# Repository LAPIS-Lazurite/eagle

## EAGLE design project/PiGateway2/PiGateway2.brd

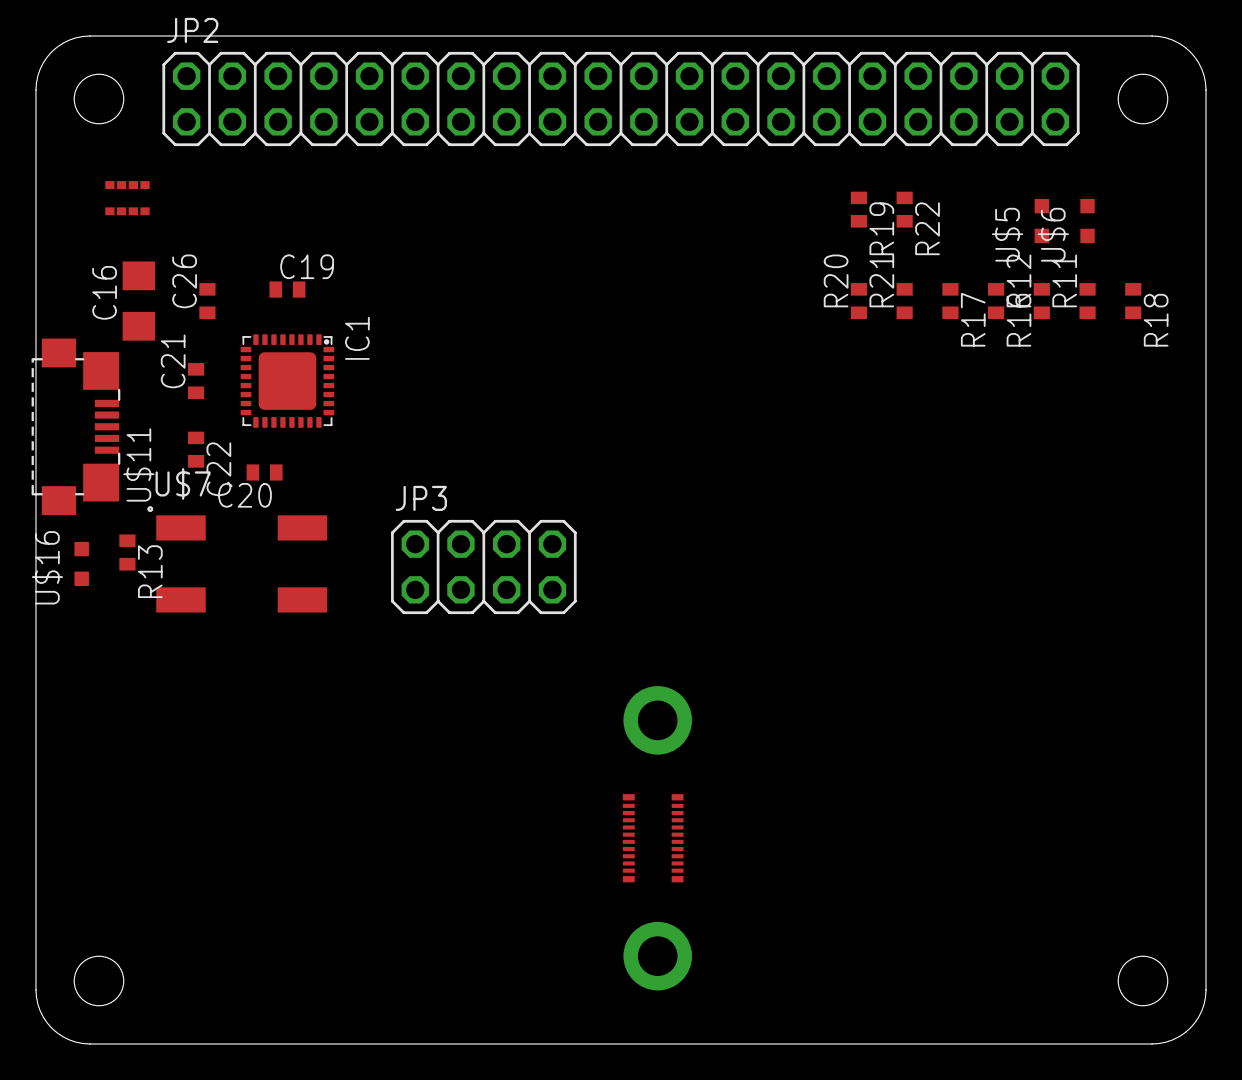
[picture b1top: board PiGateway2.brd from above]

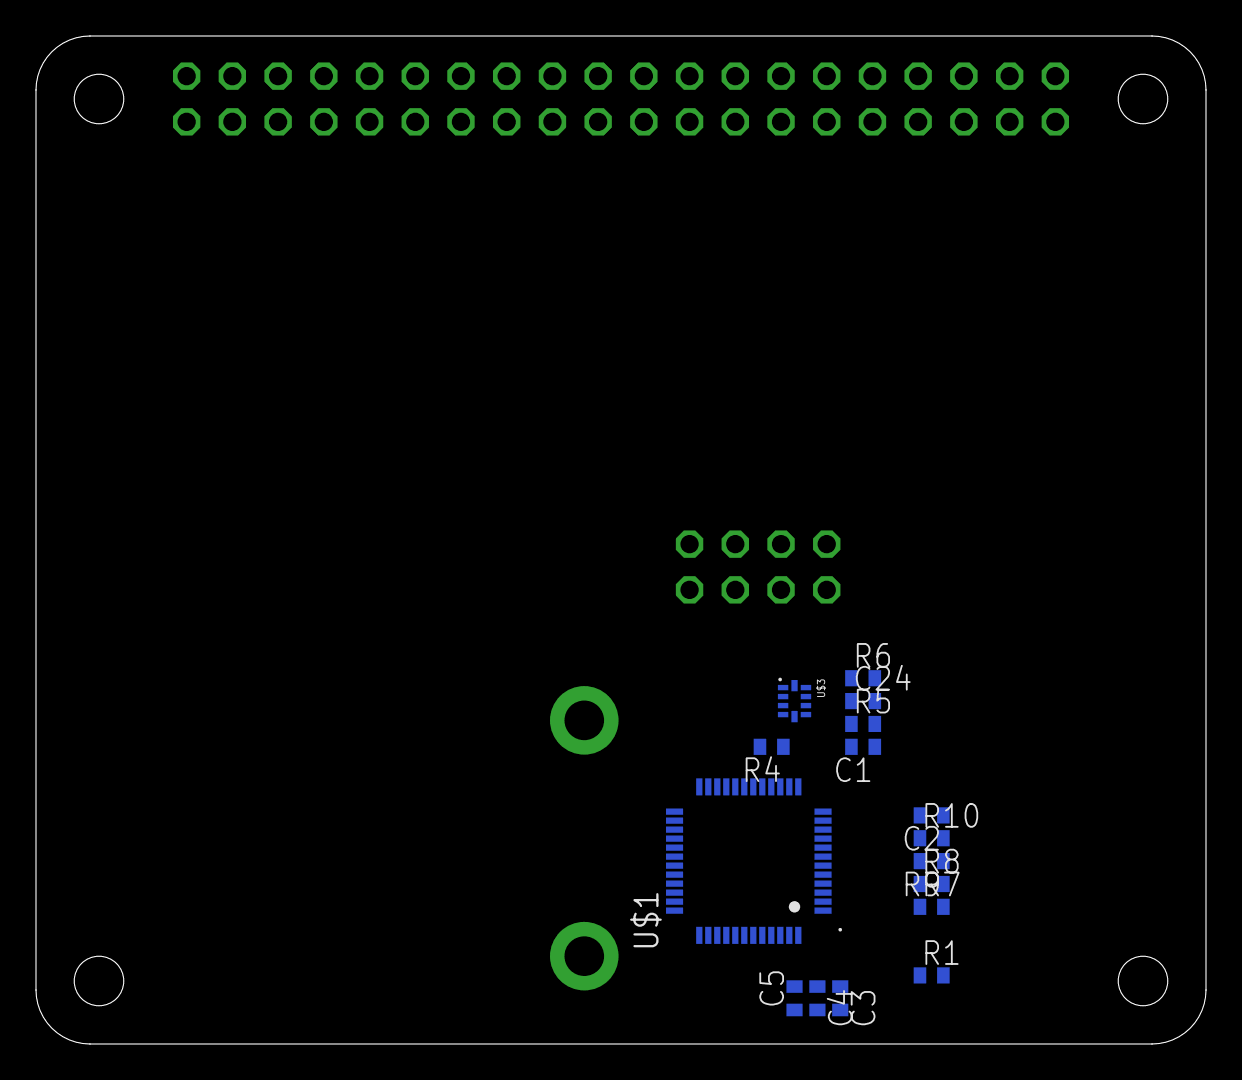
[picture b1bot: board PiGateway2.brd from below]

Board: 2 copper layers, 65.0 x 56.0 mm, 42 parts (16 on the bottom side), 46 nets, no tracks yet.

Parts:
C1, C19, C20, C24, C26: 0.1u; C0402
C2: 1u; C0402
C3: 33000p; C0402
C4, C5: 2.2u; C0402
C16: 22u; C1206
C21, C22: 47p; C0402
IC1: FT232RQ; QFN32
JP2: 2X20
JP3: 2X04
R1, R5, R6: 510; R0402
R4, R9, R10, R16, R17, R18, R19, R22: 10K; R0402
R7, R8, R11, R12, R13: 1K; R0402
R20: 0; R0402
R21: NC; R0402
U$1: ML620Q504
U$2: RT1A060AP; TSST8
U$3: TI-TS5A23159; UQFN10
U$4: DF40C-20DP-0.4V(51); BP3596A
U$5: SML-E13BC8T; SML-E1X
U$6: SML-E12Y8W; SML-E1X
U$7: SKHUALE010
U$11: ZX62R-B-5P
U$16: SML-E12U8WT86; SML-E1X

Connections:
+3V3: JP2.1, JP2.17, R11.1, R12.1, R16.1, R17.1, R18.1, R19.1, R22.1, U$4.8, U$4.9
+5V: JP2.2, JP2.4, U$2.P1, U$2.P2, U$2.P3, U$2.P6, U$2.P8
+5V/1: C1.1, C2.1, C5.1, C16.1, C19.1, C20.1, C24.1, C26.1, IC1.1, IC1.19, JP3.1, R9.1, R10.1, R13.2, U$1.12, U$1.13, U$1.44, U$2.P5, U$3.8, U$11.1
BOOT_WRITE: IC1.11, R4.1, U$3.1, U$3.5
DM: C22.1, IC1.15, U$11.2
DP: C21.1, IC1.14, U$11.3
GND: C1.2, C2.2, C3.2, C4.2, C5.2, C16.2, C19.2, C20.2, C21.2, C22.2, C24.2, C26.2, IC1.4, IC1.17, IC1.20, IC1.24, IC1.26, JP2.6, JP2.9, JP2.14, JP2.20, JP2.25, JP2.30, JP2.34, JP2.39, JP3.8, R4.2, U$1.14, U$1.45, U$3.3, U$4.3, U$4.4, U$4.5, U$4.6, U$4.17, U$4.GND1, U$7.3, U$7.4, U$11.4, U$11.5, U$11.M1, U$11.M2, U$11.M3, U$11.M4
I2C_SCL: JP2.5, R17.2, U$4.1
I2C_SDA: JP2.3, R16.2, U$4.2
LED_RX: JP2.33, U$6.C
LED_TX: JP2.31, U$5.C
MISO: JP2.21, U$4.12
MOSI: JP2.19, U$4.16
unnamed: C3.1, U$1.46
unnamed: IC1.32, U$3.2
unnamed: IC1.31, U$3.4
unnamed: IC1.30, R7.2
unnamed: C4.1, U$1.43
unnamed: R13.1, U$16.A
unnamed: IC1.2, R8.2
unnamed: IC1.22, R6.2
unnamed: IC1.21, R5.2
unnamed: R1.1, U$2.P4
unnamed: R11.2, U$6.A
unnamed: R12.2, U$5.A
P23: U$1.18, U$16.C
P30: R7.1, U$1.4
P31: R8.1, U$1.5
P34: JP3.5, R9.2, U$1.8
P35: JP3.6, R10.2, U$1.9
P36: JP3.4, U$1.10
P44: JP3.2, U$1.29
P45: JP3.3, U$1.30
P50: U$1.33, U$7.1, U$7.2
P53: JP3.7, U$1.36
RF_CSB: R20.1, R21.1, U$4.15
RF_CSB0: JP2.24, R19.2, R20.2
RF_CSB1: JP2.26, R21.2, R22.2
RF_IRQ: JP2.12, U$4.13
RF_REGPDIN: JP2.11, U$4.10
RF_RSTB: JP2.13, R18.2, U$4.11
SCLK: JP2.23, U$4.14
TEST0: U$1.41, U$3.10
TEST1N: U$1.42, U$3.6
U_TEST0: R6.1, U$3.9
U_TEST1N: R5.1, U$3.7

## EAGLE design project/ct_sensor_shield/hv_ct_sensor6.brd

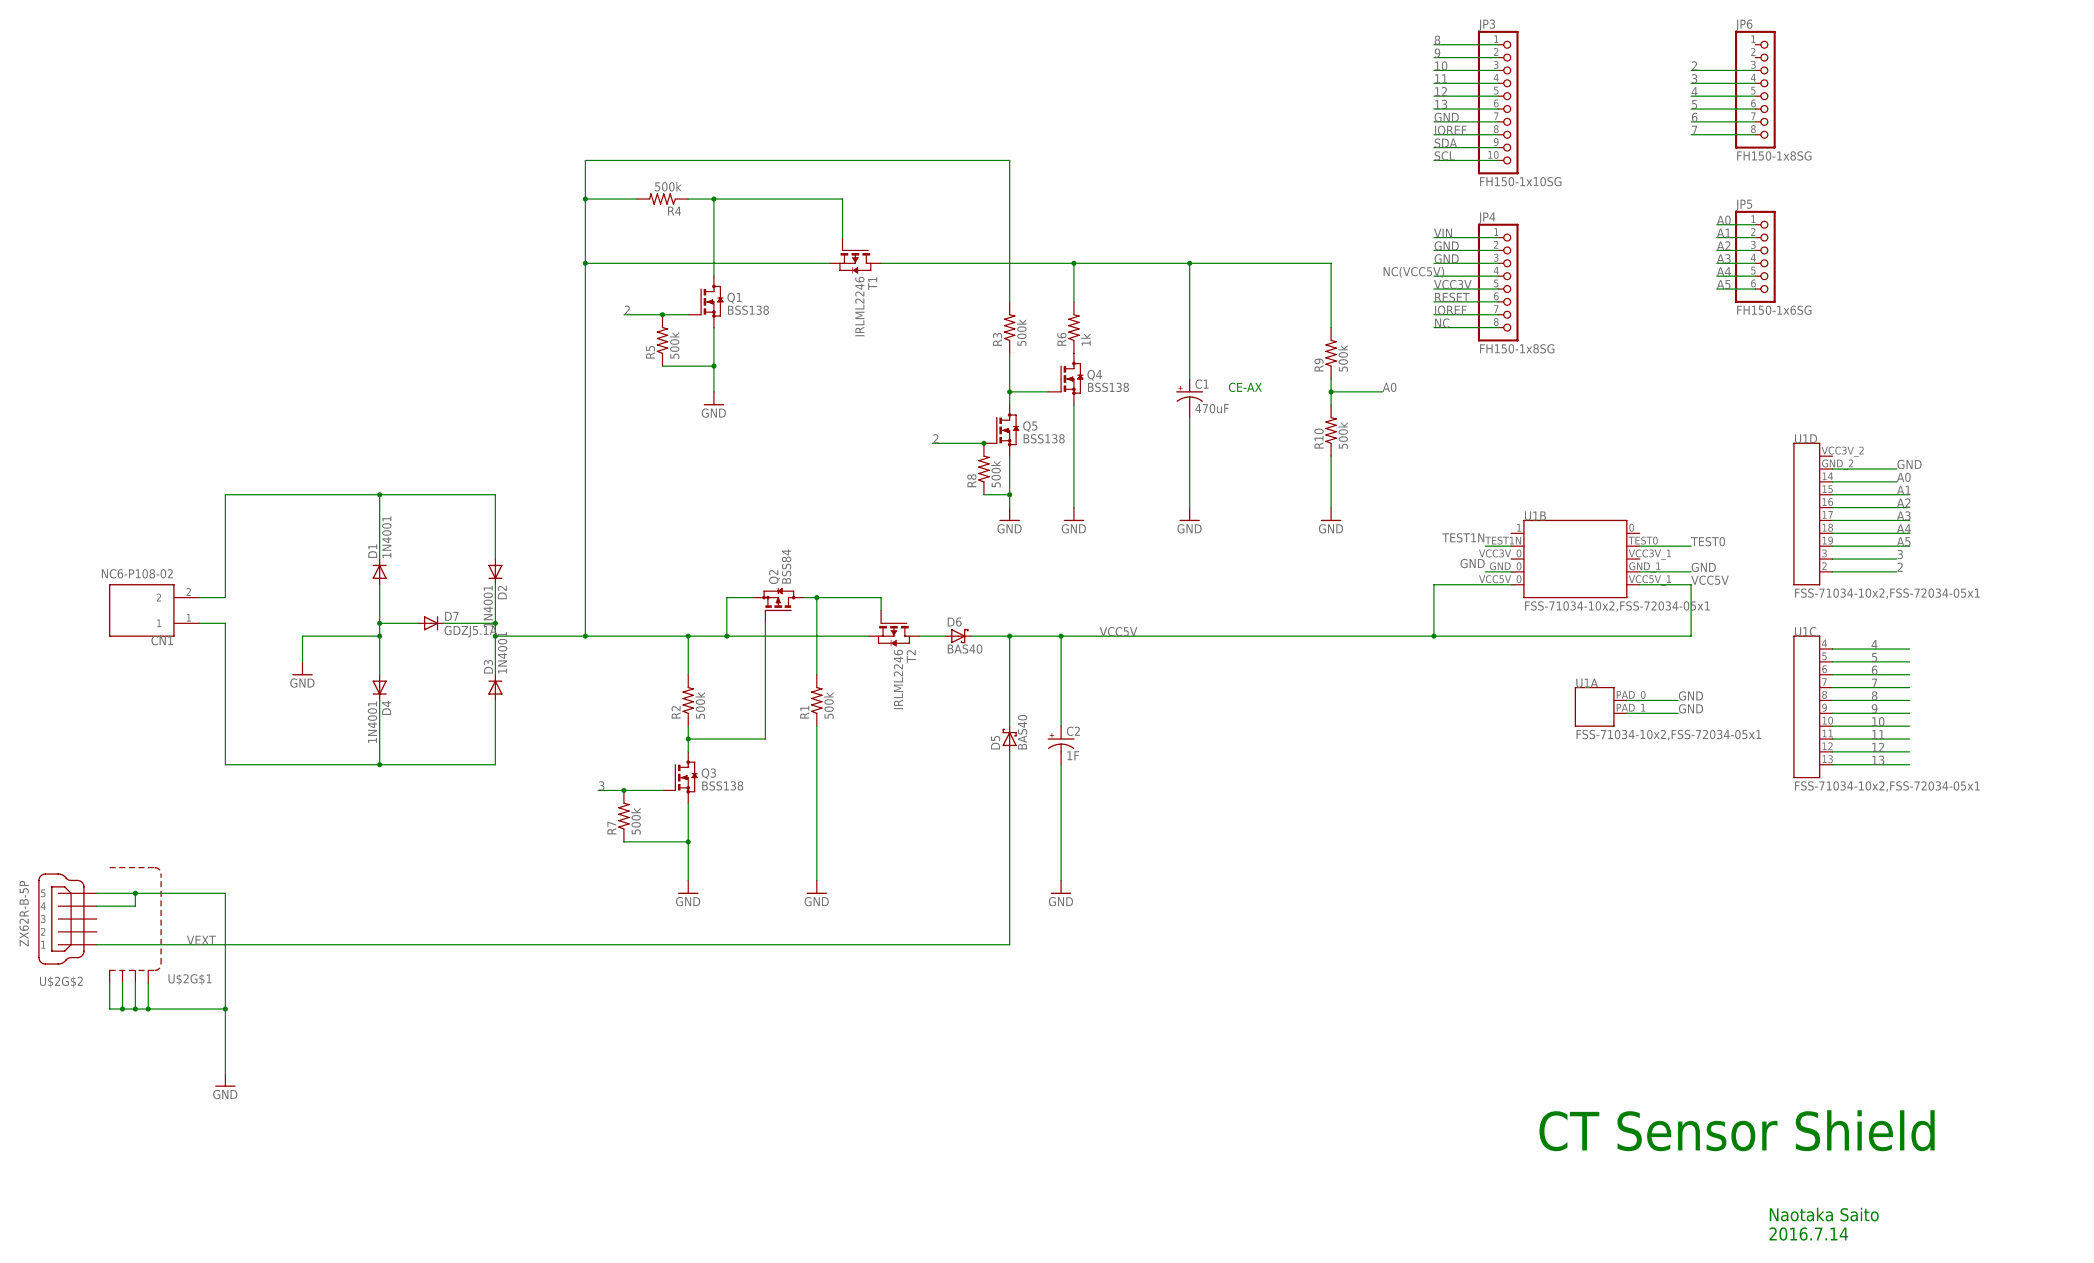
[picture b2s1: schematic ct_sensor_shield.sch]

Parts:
C1: 470uF; E5-10,5
C2: 1F; E5-20
CN1: NC6-P108-02; 2PIN
D1, D2, D3, D4: 1N4001; DO41-10
D5, D6: BAS40; SOT23
D7: GDZJ5.1A; DO34-7
JP3: FH150-1x10SG; 1X10
JP4, JP6: FH150-1x8SG; 1X08
JP5: FH150-1x6SG; 1X06
Q1, Q3, Q4, Q5: BSS138; SOT23
Q2: BSS84; SOT23
R1, R2, R3, R4, R5, R7, R8, R9, R10: 500k; R0603
R6: 1k; R0603
T1, T2: IRLML2246; SOT-23
U1: FSS-71034-10x2,FSS-72034-05x1; LAZURITE920J
U$2: ZX62R-B-5P

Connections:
2: JP6.3, Q1.1 (G), Q5.1 (G), R5.2, R8.2, U1.2
3: JP6.4, Q3.1 (G), R7.2, U1.3
4: JP6.5, U1.4
5: JP6.6, U1.5
6: JP6.7, U1.6
7: JP6.8, U1.7
8: JP3.1, U1.8
9: JP3.2, U1.9
10: JP3.3, U1.10
11: JP3.4, U1.11
12: JP3.5, U1.12
13: JP3.6, U1.13
A0: JP5.1, R9.1, R10.2, U1.14
A1: JP5.2, U1.15
A2: JP5.3, U1.16
A3: JP5.4, U1.17
A4: JP5.5, U1.18
A5: JP5.6, U1.19
GND: C1.-, C2.-, D1.A, D4.A, D7.A, JP3.7, JP4.2, JP4.3, Q1.2 (S), Q3.2 (S), Q4.2 (S), Q5.2 (S), R1.1, R5.1, R7.1, R8.1, R10.1, U1.GND_0, U1.GND_1, U1.GND_2, U1.PAD_0, U1.PAD_1, U$2.4, U$2.5, U$2.M1 (S1), U$2.M2 (S2), U$2.M3 (S3), U$2.M4 (S4)
I+: CN1.2, D1.C, D2.A
I-: CN1.1, D3.A, D4.C
IOREF: JP3.8, JP4.7
IOUT: D2.C, D3.C, D7.C, Q2.2 (S), R2.2, R3.2, R4.2, T1.2 (S), T2.2 (S)
IOUT2: D6.1 (A), T2.1 (D)
unnamed: Q2.3 (D), R1.2, T2.3 (G)
unnamed: Q2.1 (G), Q3.3 (D), R2.1
unnamed: Q1.3 (D), R4.1, T1.3 (G)
unnamed: Q4.3 (D), R6.1
unnamed: C1.+, R6.2, R9.2, T1.1 (D)
unnamed: Q4.1 (G), Q5.3 (D), R3.1
NC: JP4.8
NC(VCC5V): JP4.4
RESET: JP4.6
SCL: JP3.10
SDA: JP3.9
TEST0: U1.TEST0
TEST1N: U1.TEST1N
VCC3V: JP4.5
VCC5V: C2.+, D5.3 (C), D6.3 (C), U1.VCC5V_0, U1.VCC5V_1
VEXT: D5.1 (A), U$2.1
VIN: JP4.1

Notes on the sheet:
CE-AX
CT Sensor Shield
Naotaka Saito 2016.7.14

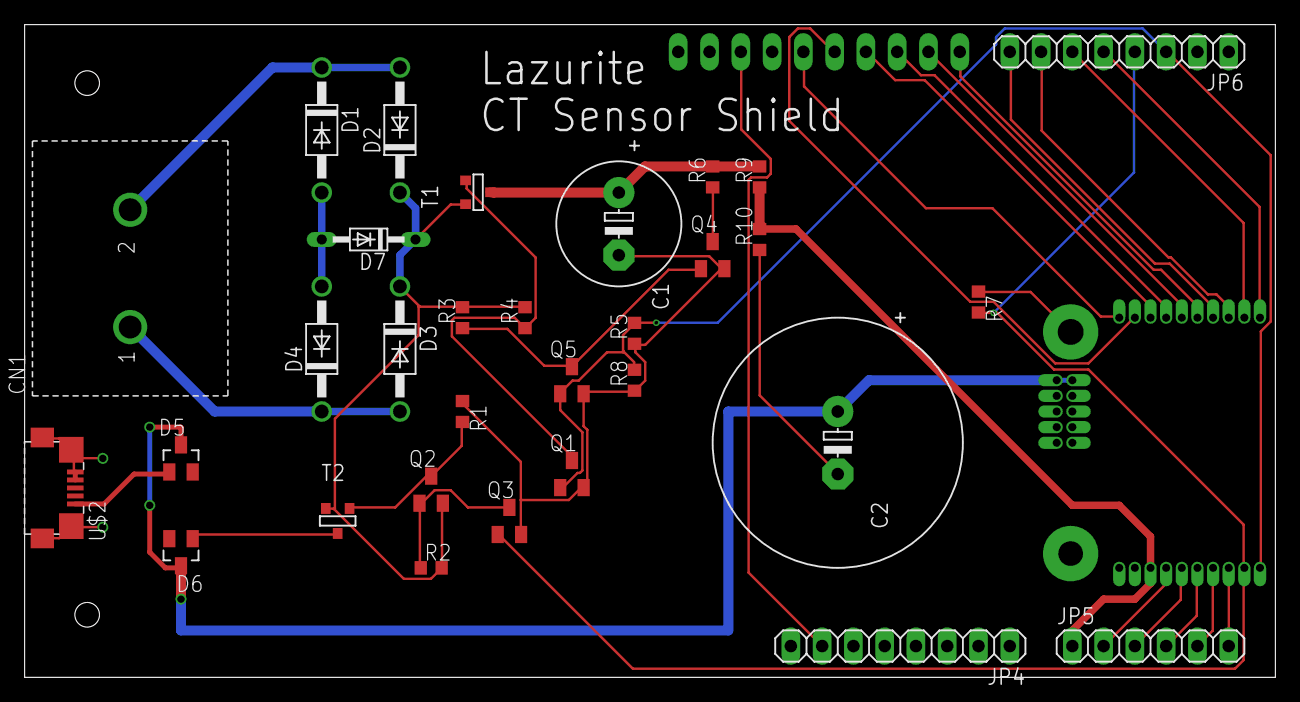
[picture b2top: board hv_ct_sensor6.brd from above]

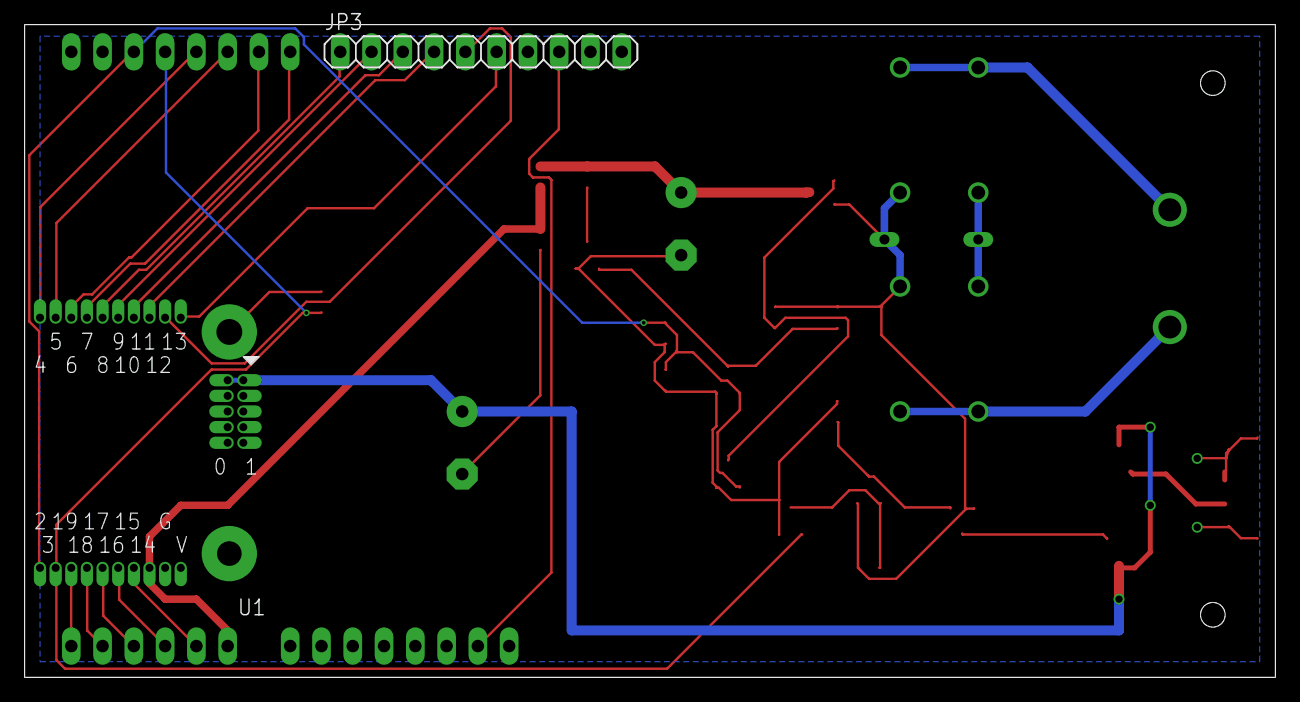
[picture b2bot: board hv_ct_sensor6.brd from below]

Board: 2 copper layers, 101.6 x 53.0 mm, 33 parts (2 on the bottom side), 32 nets.

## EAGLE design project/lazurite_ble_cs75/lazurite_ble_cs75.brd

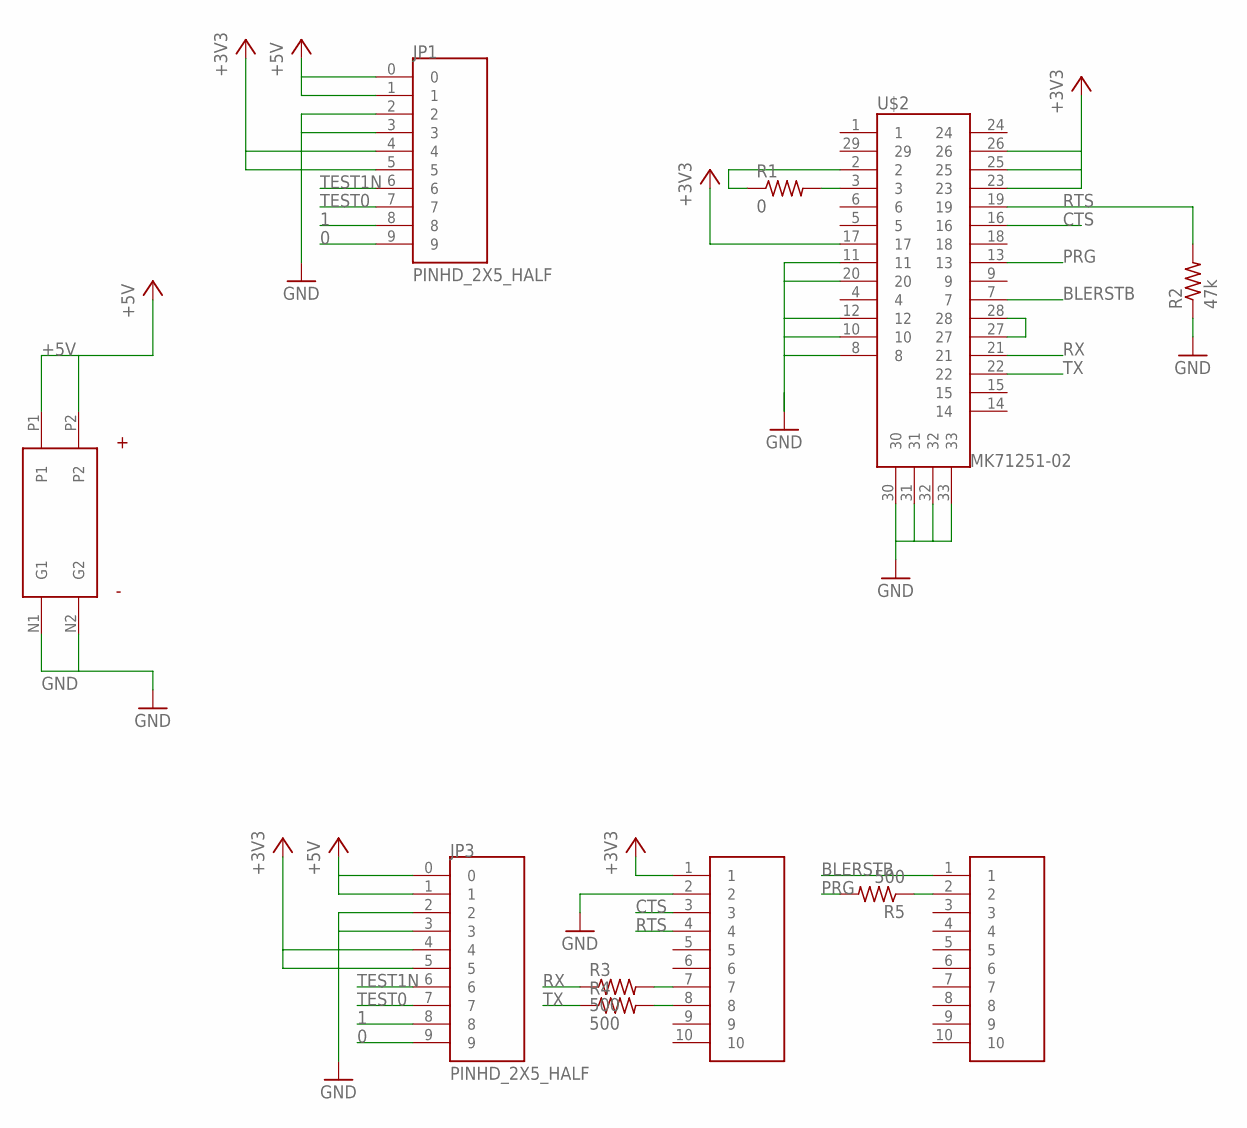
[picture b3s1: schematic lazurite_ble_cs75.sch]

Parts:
JP1, JP3: PINHD_2X5_HALF
R1: 0; R0402
R2: 47k; R0402
R3, R4, R5: 500; R0402
U$1: TAKACHI_CS75_BATTERY
U$2: MK71251-02
U$3, U$4: PINHD_1_10_HALF; PINHD_1X10_HALF

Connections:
0: JP1.9, JP3.9
1: JP1.8, JP3.8
+3V3: JP1.4, JP1.5, JP3.4, JP3.5, U$2.17, U$2.23, U$2.25, U$2.26, U$3.1
+5V: JP1.0, JP1.1, JP3.0, JP3.1, U$1.P1, U$1.P2
BLERSTB: U$2.7, U$4.1
CTS: U$2.16, U$3.3
GND: JP1.2, JP1.3, JP3.2, JP3.3, R2.1, U$1.N1 (G1), U$1.N2 (G2), U$2.8, U$2.10, U$2.11, U$2.12, U$2.20, U$2.30, U$2.31, U$2.32, U$2.33, U$3.2
unnamed: R1.2, U$2.3
unnamed: R1.1, U$2.2
unnamed: U$2.27, U$2.28
unnamed: R5.1, U$4.2
unnamed: R4.2, U$3.8
unnamed: R3.2, U$3.7
PRG: R5.2, U$2.13
RTS: R2.2, U$2.19, U$3.4
RX: R3.1, U$2.21
TEST0: JP1.7, JP3.7
TEST1N: JP1.6, JP3.6
TX: R4.1, U$2.22

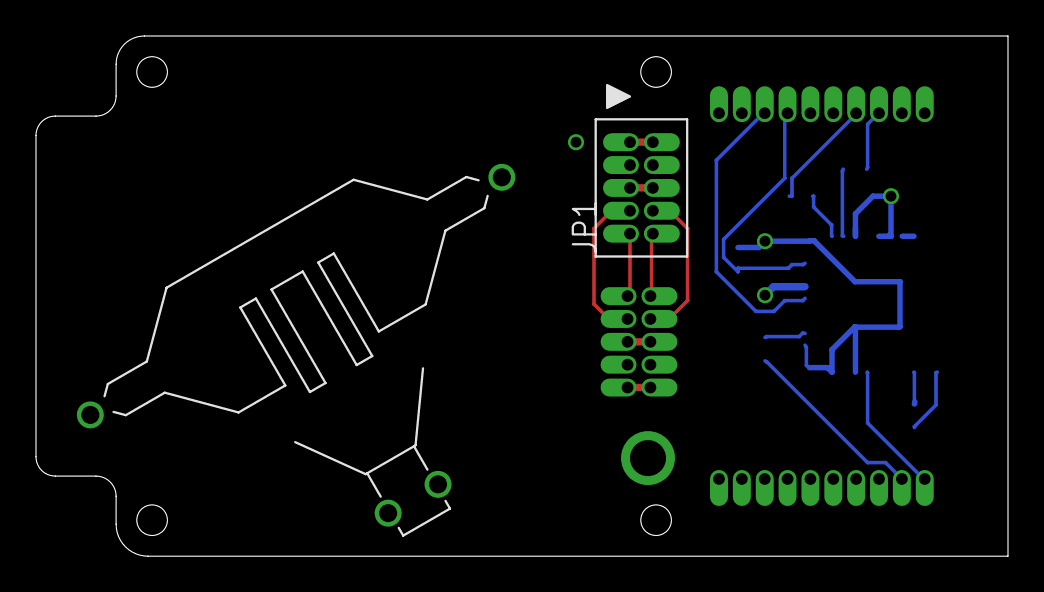
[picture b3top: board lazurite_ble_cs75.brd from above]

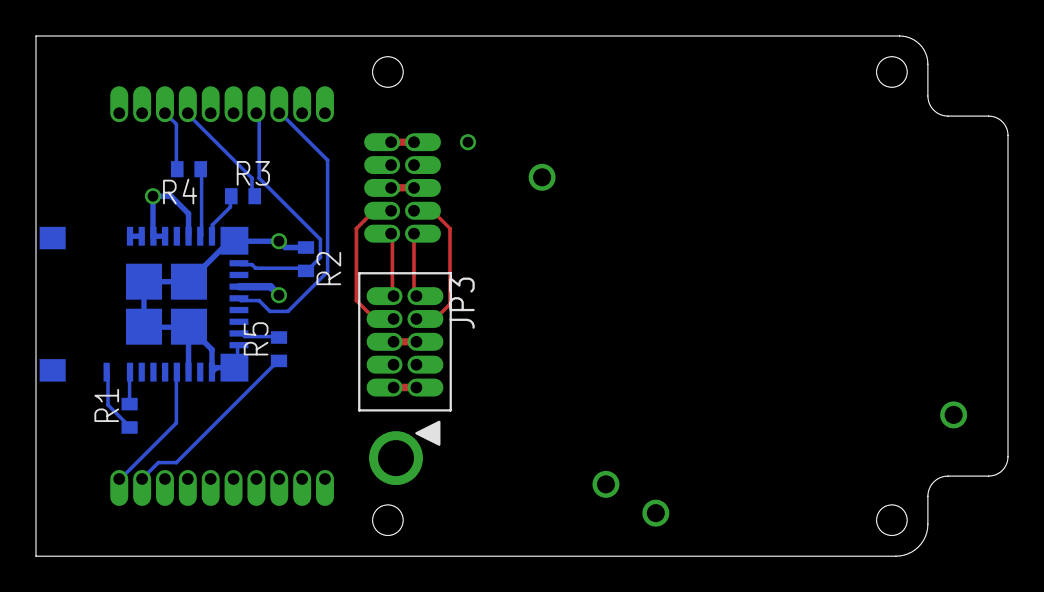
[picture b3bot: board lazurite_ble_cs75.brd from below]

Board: 4 copper layers, 54.0 x 28.9 mm, 11 parts (9 on the bottom side), 19 nets.
